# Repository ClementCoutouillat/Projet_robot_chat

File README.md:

# Projet_robot_chat

Projet fait par Quentin Henriet, Bastien Chinianga, Jiang Kaixuan, Jangbo Wang et Clément Coutouillat
Dans ce projet, nous devons réaliser un robot à propulsion différentielle à deux roues pour jouer au jeu du chat et de la souris. Lorsque le robot est le chat, il poursuit la souris, et lorsqu'il est la souris, il fuit le chat. Pour accomplir ce jeu, nous devons réaliser les parties suivantes :

- Le robot doit pouvoir changer de rôle entre chat et souris dans le jeu. Lorsque deux robots entrent en collision, leurs rôles changent - capteur de détection de collision.
- Le robot doit pouvoir se déplacer dans un environnement avec des limites, donc nous avons besoin d'un capteur de détection de bord - capteur de détection de bord.
- Le robot doit pouvoir détecter le chat ou la souris sur le terrain, donc nous avons besoin d'un capteur pour détecter les objets sur le terrain - capteur LIDAR.

## Ydlidar

Nous utilisons le LIDAR YDLIDAR X4 pour détecter l'autre robot sur le terrain.
D'après le manuel de données de YDLIDAR, nous savons que YDLIDAR utilise Uart pour la communication. Dans le manuel de développement, nous pouvons obtenir le format des données du LIDAR, comme illustré ci-dessous :
Lorsque nous envoyons la commande A5 60 au LIDAR, il renvoie une trame de données, dont le format est illustré ci-dessous :

Ensuite, en suivant la méthode d'analyse du manuel de développement, nous obtenons les angles et les distances des obstacles de 0 à 360 degrés autour du robot, ce qui nous permet de localiser l'autre robot.

## Stratégie

Dans le jeu, lorsque le robot est le chat, il doit poursuivre la souris, et lorsqu'il est la souris, il doit fuir le chat. Donc, selon le rôle du robot, nous avons besoin de stratégies différentes pour contrôler le mouvement du robot.

### Stratégie Chat

Lorsque le robot est le chat, il doit poursuivre la souris. Nous devons donc faire bouger le robot dans la direction de la souris. Tout d'abord, nous contrôlons la rotation du robot en calculant la différence d'angle entre le robot et la souris. Lorsque la souris se trouve entre 0 et 180 degrés, nous faisons tourner le robot à gauche. Lorsque l'autre robot se trouve entre 180 et 360 degrés, nous faisons tourner le robot

à droite. Une fois que le robot est orienté correctement, nous le faisons avancer jusqu'à ce qu'il entre en collision avec la souris. À ce moment-là, le rôle du robot change : le robot devient la souris et l'autre robot devient le chat. Nous pouvons alors utiliser la stratégie de la souris pour contrôler le mouvement du robot.

### Stratégie Souris

Lorsque le robot est la souris, il doit fuir le chat. Nous devons donc faire éloigner le robot du chat. Lorsqu'un chat se trouve à moins de 50 cm du robot et qu'il est situé entre 0 et 180 degrés, nous faisons tourner le robot à gauche de 90 degrés, puis le faisons avancer sur une certaine distance avant de le faire tourner à droite de 90 degrés. Cela permet au robot de s'éloigner du chat. Lorsque la distance entre le robot et le chat dépasse 50 cm, nous arrêtons le mouvement du robot. Lorsque le chat est situé entre 180 et 360 degrés, nous faisons tourner le robot à droite de 90 degrés, puis à gauche de 90 degrés, pour lui permettre de s'éloigner du chat.

## Moteur

Nous utilisons un robot à propulsion différentielle à deux roues, donc nous devons contrôler la vitesse des roues gauche et droite pour diriger le robot. Nous utilisons un moteur à courant continu à engrenages avec encodeur, dont la vitesse maximale est de 300 RPM.

### Avancer

Pour faire avancer le robot en ligne droite, nous contrôlons les vitesses des roues gauche et droite pour qu'elles soient identiques.

### Tourner

Le robot tourne en contrôlant la différence de vitesse entre les roues gauche et droite. Lorsque les vitesses des roues sont différentes, le robot tourne.

Nous utilisons une vitesse fixe pour contrôler la direction du robot. Lorsque le robot doit tourner à gauche, nous fixons la vitesse de la roue gauche à 0 et celle de la roue droite à la vitesse maximale. Lorsque le robot doit tourner à droite, nous fixons la vitesse de la roue droite à 0 et celle de la roue gauche à la vitesse maximale. Le temps nécessaire pour tourner est calculé avec la formule suivante :

<br />
leftWheelLinearVelocity = wheelDiameter * PI * leftWheelRPM / 60 ;
<br />
rightWheelLinearVelocity = wheelDiameter * PI * rightWheelRPM / 60 ;
<br />
angulaVelocity = (leftWheellinearVelocity - rightWheellinearVelocity) / WheelDistance ;
<br />
Timer = Angle(0-360) *PI / 180 / angulaVelocity ;

### Distance Control

La distance parcourue par le robot est contrôlée en gérant le temps de fonctionnement du robot. Lorsque le robot fonctionne pendant le temps que nous avons défini, il s'arrête. Cela permet de contrôler la distance parcourue par le robot. Le temps est calculé avec la formule suivante :
<br />
Timer = Distance / (WheelDiameter \* PI) / Vitesse ;

### Commande

Dans notre code pour manipuler le moteur, nous avons écrit deux fonctions. La première permet de contrôler directement la vitesse du moteur. Pour que le robot réponde plus rapidement aux commandes d'arrêt et d'accélération, nous avons également écrit une seconde fonction d'asservissement, qui utilise l'algorithme PID pour contrôler la rotation du moteur. Toutes les 100 ms, nous calculons la vitesse actuelle et fournissons un feedback sur la vitesse pour nous informer de la vitesse actuelle de rotation du moteur, ce qui nous permet de calculer plus précisément la position actuelle du robot et la distance parcourue. L'entrée du contrôleur PID est la vitesse cible du robot, et la sortie est la vitesse des roues gauche et droite du robot.

## Border

Pour les capteurs de bordure nous avons décidé d'utiliser les interruptions extérieures afin que la plus grande priorité possible et ne pas être interrompu durant le traitement de la détection de bordure. L'objectif était de pouvoir reculer et de tourner de 90 ou 180 degrés. Des tests ont été effectué sur une autre carte afin de vérifier le bon fonctionnement des fonctions. Malheureusement, les fonctions n'ont pas été implémenté sur la carte car les capteurs infrarouges étaient inutilisables et nous n'avions pas d'autres.

## Contact

Les capteurs de contact sont aussi branché sur les entrées GPIO du microprocesseur. Le contact permettant de gérer le mode chat ou souris, nous avons aussi décidé de les mettre en interruptions extérieur car ça simplifie le code avec juste une interruption qui préempte le code et une gestion de l'interruption. Il faut aussi mettre l'interruption des capteurs de bordure avec une plus haute priorité car c'est plus important de garder le robot sur le terrain que de savoir si on se fait toucher. Dans l'IOC il faut faire attention à comment sont régler les GPIO. Ils sont soit en pull-up ou pull-down. Afin de pour pouvoir résoudre le problème du fonctionnement des  capteurs de contact nous avons décidé de "simuler" le fait d'être touchés par un autre robot. C'est-à-dire quand nous sommes trop proches d'un autre robot nous considérons que nous avons été touché par celui-ci, car sinon le robot ne change jamais d'état.

## Accéléromètre

Au cours du projet nous avons utilisé deux cartes différentes. Sur la première, nous avions pensé à utiliser une centrale inertielle donc un accéléromètre et un gyroscope. Nous avons donc commencé l'écriture d'un driver( un .c et un .h) pour utiliser cet IMU. Malheureusement sur la nouvelle carte il n'y avait plus la possibilité d'utiliser un IMU, et vu l'inutilité de cette partie nous avons décidé de ne pas la mettre sur le github mais de quand même  mentionner le fait qu'un début de driver a été fait.

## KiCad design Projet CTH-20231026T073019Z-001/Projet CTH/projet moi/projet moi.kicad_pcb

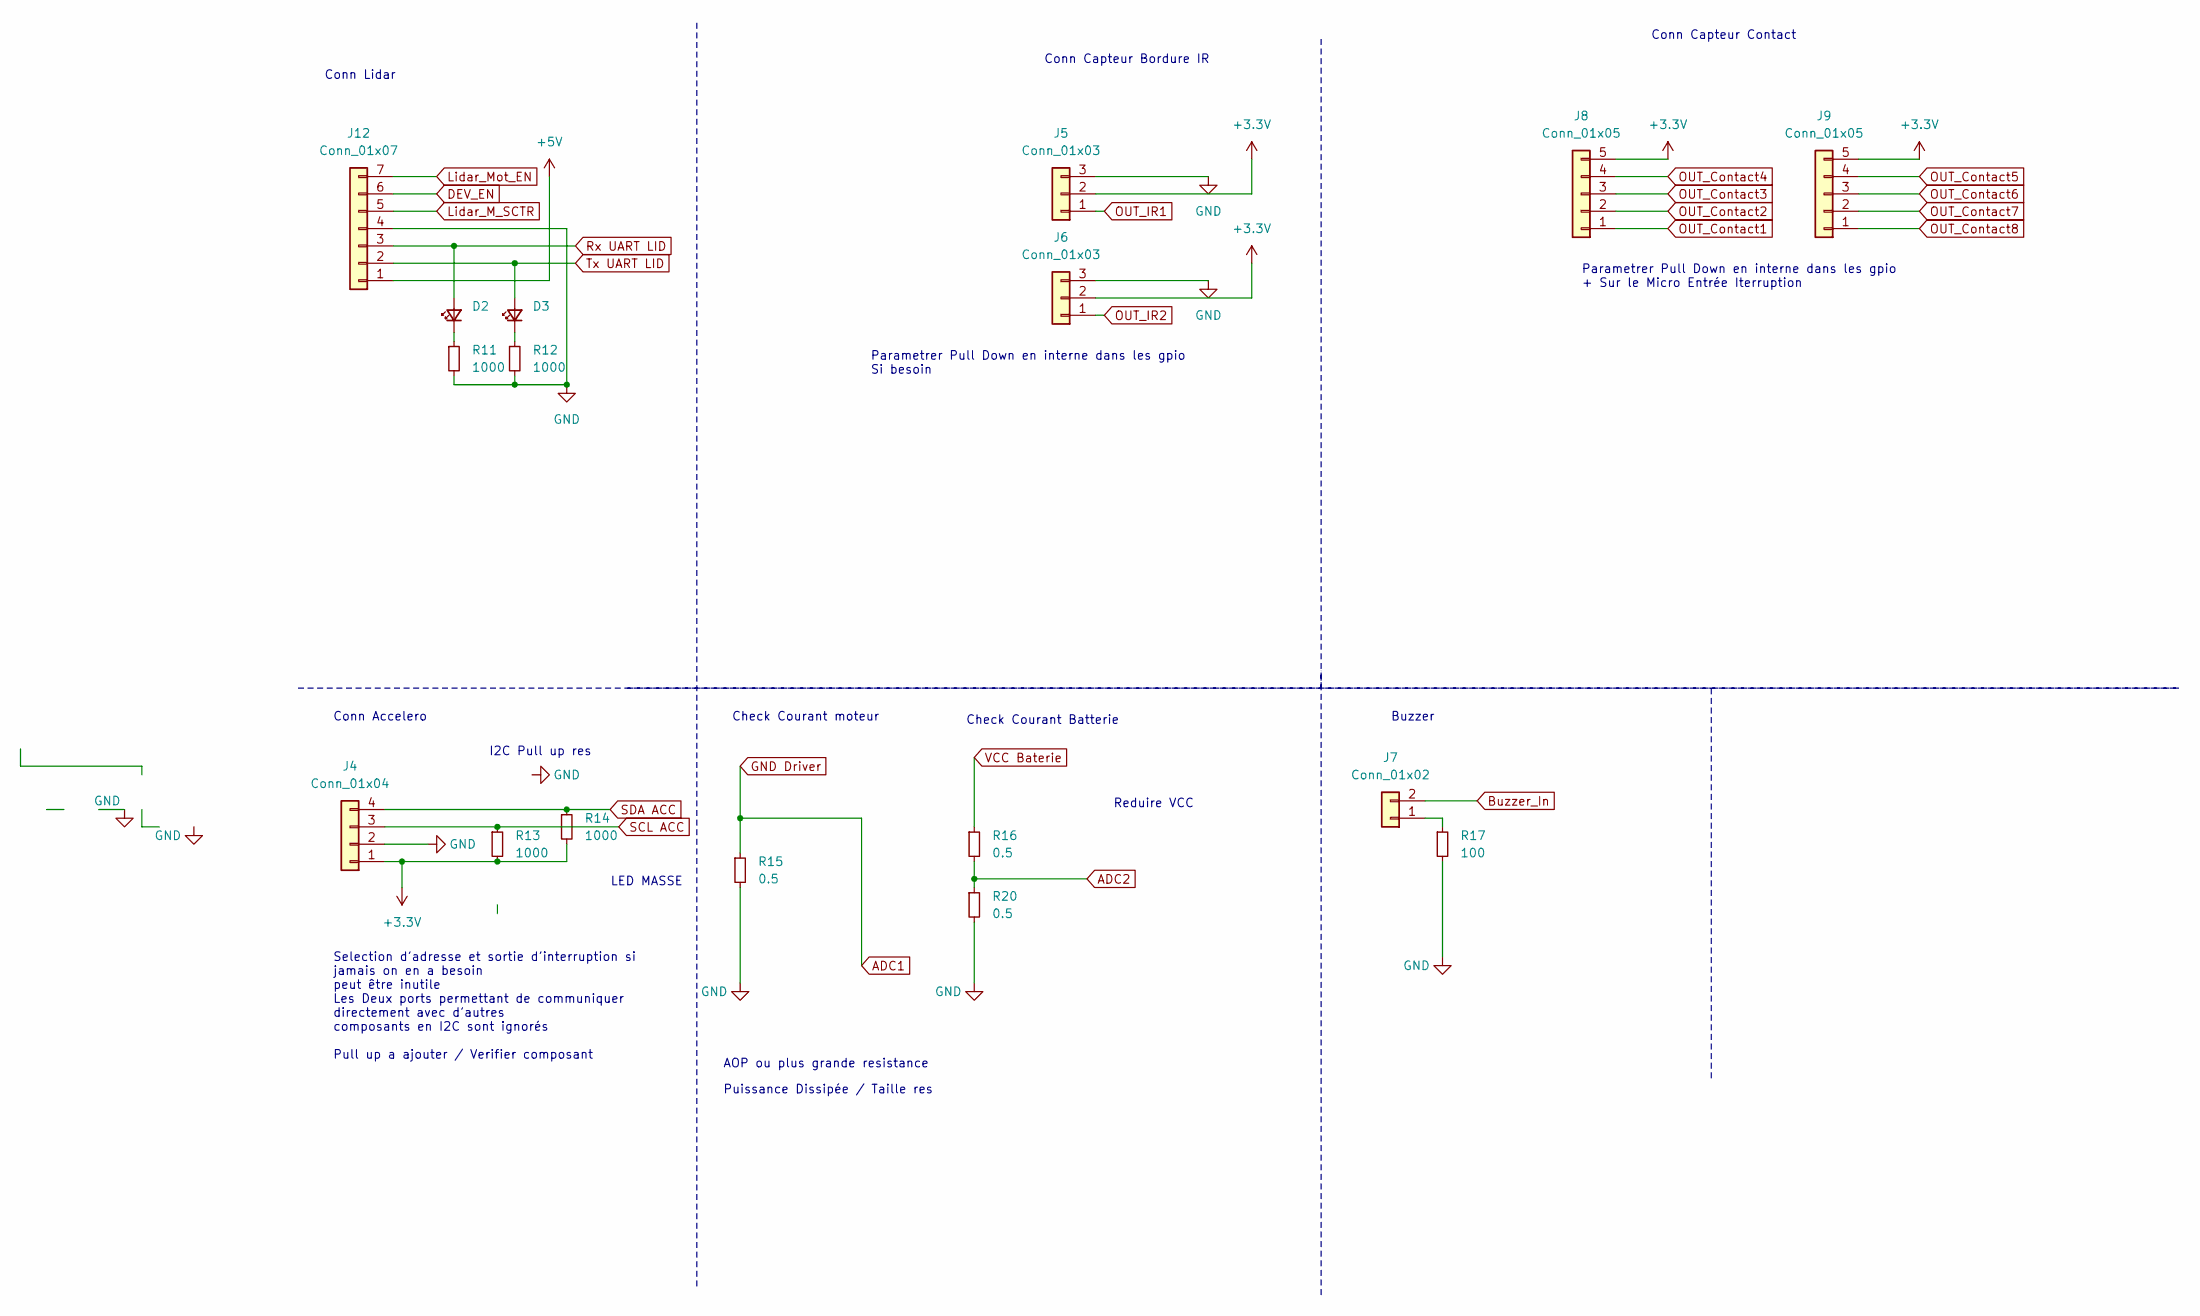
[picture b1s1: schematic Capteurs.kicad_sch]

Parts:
D2, D3: LED_Small; LED_0603_1608Metric_Pad1.05x0.95mm_HandSolder
J4: Conn_01x04; JST_EH_S4B-EH_1x04_P2.50mm_Horizontal
J5, J6: Conn_01x03; JST_XH_S3B-XH-A_1x03_P2.50mm_Horizontal
J7: Conn_01x02; JST_XH_S2B-XH-A_1x02_P2.50mm_Horizontal
J8, J9: Conn_01x05; JST_XH_S5B-XH-A_1x05_P2.50mm_Horizontal
J12: Conn_01x07; JST_XH_S7B-XH-A_1x07_P2.50mm_Horizontal
R11, R12, R13, R14: 1000; R_0603_1608Metric_Pad0.98x0.95mm_HandSolder
R15, R16, R20: 0.5; R_0603_1608Metric_Pad0.98x0.95mm_HandSolder
R17: 100; R_0603_1608Metric_Pad0.98x0.95mm_HandSolder

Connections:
7.2V: R16.1; also elsewhere on the board
+3.3V: J4.1, J5.2, J6.2, J8.5, J9.5, R13.2, R14.2; also elsewhere on the board
+5V: J12.1; also elsewhere on the board
ADC1: R15.1; also elsewhere on the board
ADC2: R16.2, R20.1; also elsewhere on the board
DEV_EN: J12.6; also elsewhere on the board
GND: J4.2, J5.3, J6.3, J12.4, R11.2, R12.2, R15.2, R17.2, R20.2; also elsewhere on the board
Lidar_M_SCTR: J12.5
Lidar_Mot_EN: J12.7
unnamed: D2.1 (K), R11.1
unnamed: D3.1 (K), R12.1
unnamed: J7.1, R17.1
OUT_Contact1: J8.1; also elsewhere on the board
OUT_Contact2: J8.2; also elsewhere on the board
OUT_Contact3: J8.3; also elsewhere on the board
OUT_Contact4: J8.4; also elsewhere on the board
OUT_Contact5: J9.4; also elsewhere on the board
OUT_Contact6: J9.3; also elsewhere on the board
OUT_Contact7: J9.2; also elsewhere on the board
OUT_Contact8: J9.1; also elsewhere on the board
OUT_IR1: J5.1; also elsewhere on the board
OUT_IR2: J6.1; also elsewhere on the board
Rx UART LID: D2.2 (A), J12.3; also elsewhere on the board
SCL ACC: J4.3, R13.1; also elsewhere on the board
SDA ACC: J4.4, R14.1; also elsewhere on the board
Tx UART LID: D3.2 (A), J12.2; also elsewhere on the board

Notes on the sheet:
Reduire VCC
Check Courant moteur
Buzzer
Parametrer Pull Down en interne dans les gpio + Sur le Micro Entrée Iterruption
Check Courant Batterie
AOP ou plus grande resistance
Puissance Dissipée / Taille res
Conn Lidar
Conn Accelero
Conn Capteur Contact
Parametrer Pull Down en interne dans les gpio Si besoin
I2C Pull up res
Selection d'adresse et sortie d'interruption si jamais on en a besoin peut être inutile Les Deux ports permettant de communiquer directement avec d'autres composants en I2C sont ignorés Pull up a ajouter / Verifier composant
LED MASSE
Conn Capteur Bordure IR

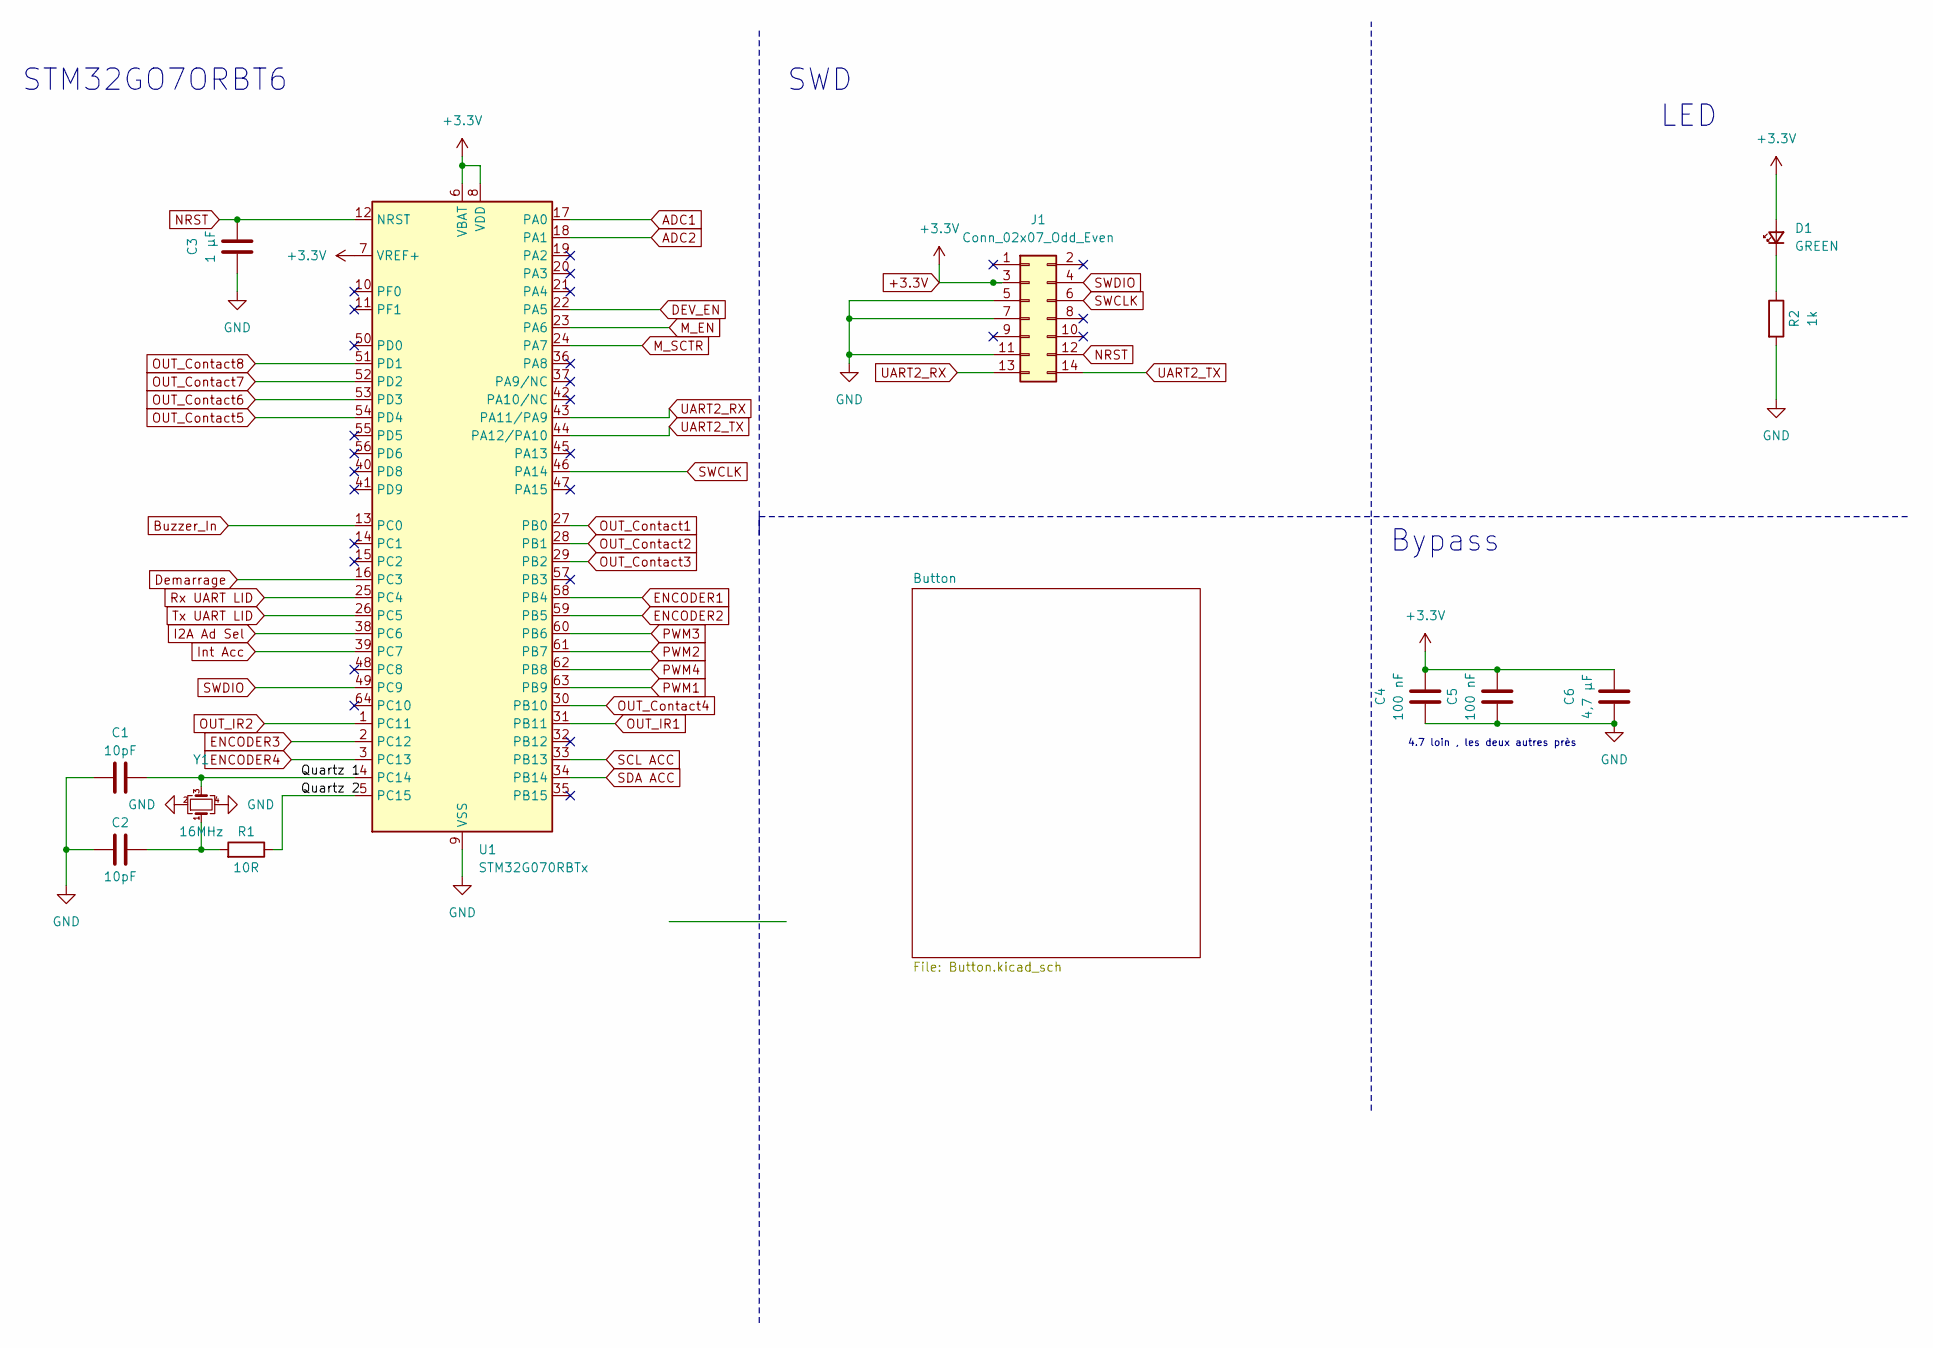
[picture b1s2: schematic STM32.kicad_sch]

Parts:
C1, C2: 10pF; C_0603_1608Metric_Pad1.08x0.95mm_HandSolder
C3: 1 µF; C_0603_1608Metric_Pad1.08x0.95mm_HandSolder
C4, C5: 100 nF; C_0603_1608Metric_Pad1.08x0.95mm_HandSolder
C6: 4,7 µF; C_0603_1608Metric_Pad1.08x0.95mm_HandSolder
D1: GREEN; LED_0603_1608Metric_Pad1.05x0.95mm_HandSolder
J1: Conn_02x07_Odd_Even; Molex_Nano-Fit_105314-xx14_2x07_P2.50mm_Horizontal
R1: 10R; R_0603_1608Metric_Pad0.98x0.95mm_HandSolder
R2: 1k; R_0603_1608Metric_Pad0.98x0.95mm_HandSolder
U1: STM32G070RBTx; LQFP-64_10x10mm_P0.5mm
Y1: 16MHz; Crystal_SMD_EuroQuartz_MT-4Pin_3.2x2.5mm

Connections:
+3.3V: C4.2, C5.2, C6.2, D1.2 (A), J1.3, U1.6 (VBAT), U1.7 (VREF+), U1.8 (VDD); also elsewhere on the board
/STM32/Quartz 1: C1.2, U1.4 (PC14), Y1.3
/STM32/Quartz 2: R1.1, U1.5 (PC15)
ADC1: U1.17 (PA0); also elsewhere on the board
ADC2: U1.18 (PA1); also elsewhere on the board
Buzzer_In: U1.13 (PC0)
DEV_EN: U1.22 (PA5); also elsewhere on the board
Demarrage: U1.16 (PC3); also elsewhere on the board
ENCODER1: U1.58 (PB4); also elsewhere on the board
ENCODER2: U1.59 (PB5); also elsewhere on the board
ENCODER3: U1.2 (PC12); also elsewhere on the board
ENCODER4: U1.3 (PC13); also elsewhere on the board
GND: C1.1, C2.1, C3.1, C4.1, C5.1, C6.1, J1.5, J1.7, J1.11, R2.2, U1.9 (VSS), Y1.2, Y1.4; also elsewhere on the board
I2A Ad Sel: U1.38 (PC6)
Int Acc: U1.39 (PC7)
M_EN: U1.23 (PA6)
M_SCTR: U1.24 (PA7)
NRST: C3.2, J1.12, U1.12 (NRST); also elsewhere on the board
unnamed: C2.2, R1.2, Y1.1
unnamed: D1.1 (K), R2.1
OUT_Contact1: U1.27 (PB0); also elsewhere on the board
OUT_Contact2: U1.28 (PB1); also elsewhere on the board
OUT_Contact3: U1.29 (PB2); also elsewhere on the board
OUT_Contact4: U1.30 (PB10); also elsewhere on the board
OUT_Contact5: U1.54 (PD4); also elsewhere on the board
OUT_Contact6: U1.53 (PD3); also elsewhere on the board
OUT_Contact7: U1.52 (PD2); also elsewhere on the board
OUT_Contact8: U1.51 (PD1); also elsewhere on the board
OUT_IR1: U1.31 (PB11); also elsewhere on the board
OUT_IR2: U1.1 (PC11); also elsewhere on the board
PWM1: U1.63 (PB9); also elsewhere on the board
PWM2: U1.61 (PB7); also elsewhere on the board
PWM3: U1.60 (PB6); also elsewhere on the board
PWM4: U1.62 (PB8); also elsewhere on the board
Rx UART LID: U1.25 (PC4); also elsewhere on the board
SCL ACC: U1.33 (PB13); also elsewhere on the board
SDA ACC: U1.34 (PB14); also elsewhere on the board
SWCLK: J1.6, U1.46 (PA14)
SWDIO: J1.4, U1.49 (PC9)
Tx UART LID: U1.26 (PC5); also elsewhere on the board
UART2_RX: J1.13, U1.43 (PA11/PA9)
UART2_TX: J1.14, U1.44 (PA12/PA10)

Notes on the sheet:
STM32GO7ORBT6
Bypass
LED
SWD
4.7 loin , les deux autres près

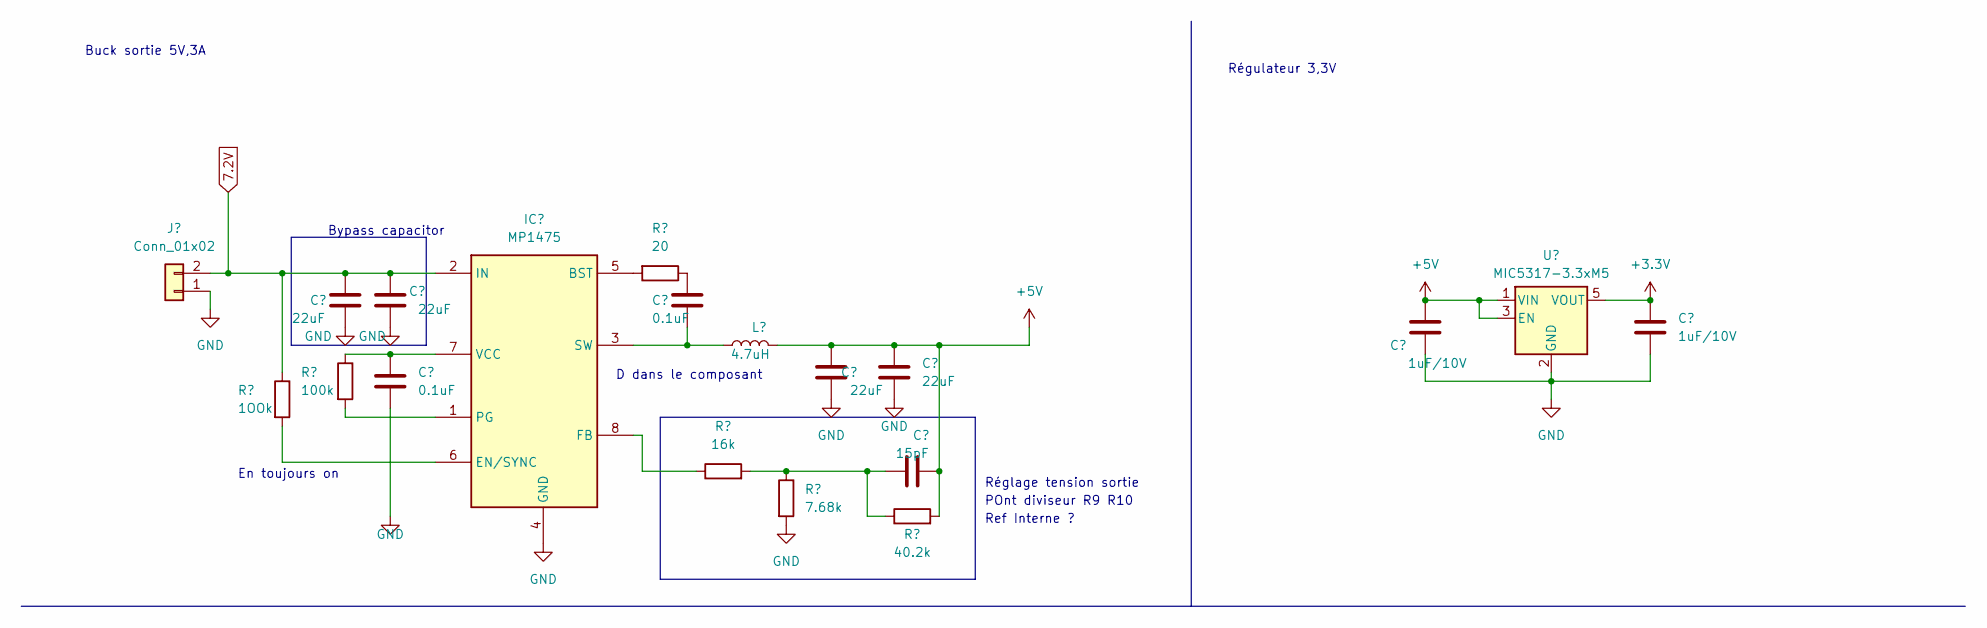
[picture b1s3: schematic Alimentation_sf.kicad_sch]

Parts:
C11, C12, C15, C16: 22uF; C_0603_1608Metric_Pad1.08x0.95mm_HandSolder
C13, C14: 0.1uF; C_0603_1608Metric_Pad1.08x0.95mm_HandSolder
C17: 15pF; C_0603_1608Metric_Pad1.08x0.95mm_HandSolder
C18, C19: 1uF/10V; C_0603_1608Metric_Pad1.08x0.95mm_HandSolder
IC1: MP1475; SOT65P280X100-8N; Mouser Part Number 946-MP1475SGJ-P
J2: Conn_01x02; JST_XH_S2B-XH-A_1x02_P2.50mm_Horizontal
L2: 4.7uH; L_0603_1608Metric_Pad1.05x0.95mm_HandSolder
R5: 1OOk; R_0603_1608Metric_Pad0.98x0.95mm_HandSolder
R6: 100k; R_0603_1608Metric_Pad0.98x0.95mm_HandSolder
R7: 20; R_0603_1608Metric_Pad0.98x0.95mm_HandSolder
R8: 16k; R_0603_1608Metric_Pad0.98x0.95mm_HandSolder
R9: 7.68k; R_0603_1608Metric_Pad0.98x0.95mm_HandSolder
R10: 40.2k; R_0603_1608Metric_Pad0.98x0.95mm_HandSolder
U2: MIC5317-3.3xM5; SOT-23-5

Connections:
7.2V: C11.1, C12.1, IC1.2 (IN), J2.2, R5.1; also elsewhere on the board
+3.3V: C19.1, U2.5 (VOUT); also elsewhere on the board
+5V: C15.1, C16.1, C17.2, C18.1, L2.2, R10.2, U2.1 (VIN), U2.3 (EN); also elsewhere on the board
GND: C11.2, C12.2, C13.2, C15.2, C16.2, C18.2, C19.2, IC1.4 (GND), J2.1, R9.2, U2.2 (GND); also elsewhere on the board
unnamed: C14.1, R7.1
unnamed: C17.1, R8.2, R9.1, R10.1
unnamed: IC1.5 (BST), R7.2
unnamed: IC1.6 (EN/SYNC), R5.2
unnamed: IC1.8 (FB), R8.1
unnamed: IC1.1 (PG), R6.2
unnamed: C14.2, IC1.3 (SW), L2.1
unnamed: C13.1, IC1.7 (VCC), R6.1

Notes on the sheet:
Bypass capacitor
POnt diviseur R9 R10
D dans le composant
En toujours on
Réglage tension sortie
Buck sortie 5V,3A
Régulateur 3,3V
Ref Interne ?

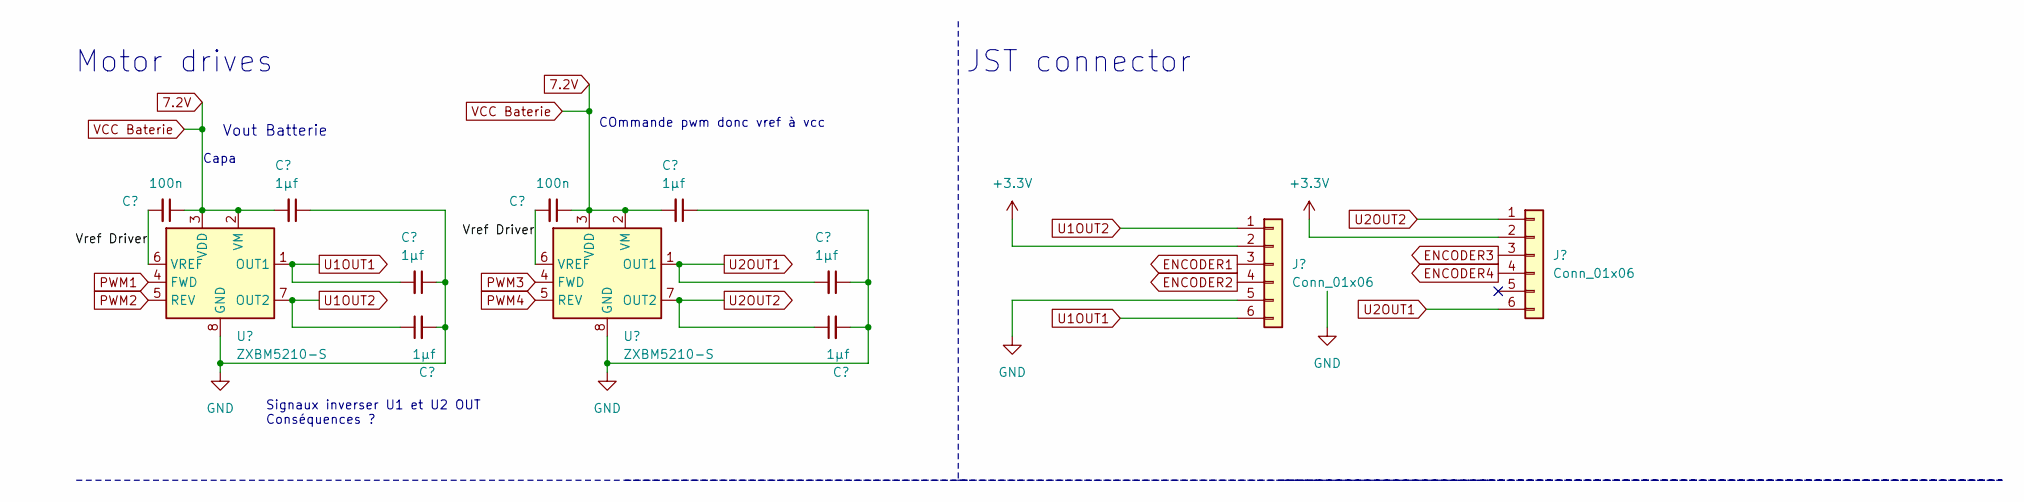
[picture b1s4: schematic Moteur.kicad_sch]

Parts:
C20, C21, C22, C23, C24, C25: 1µf; C_0603_1608Metric_Pad1.08x0.95mm_HandSolder
C27, C28: 100n; C_0603_1608Metric_Pad1.08x0.95mm_HandSolder
J10, J11: Conn_01x06; JST_XH_S6B-XH-A_1x06_P2.50mm_Horizontal
U3, U4: ZXBM5210-S; SOIC-8_3.9x4.9mm_P1.27mm

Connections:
7.2V: C20.2, C23.2, C27.1, C28.1, U3.2 (VM), U3.3 (VDD), U4.2 (VM), U4.3 (VDD); also elsewhere on the board
+3.3V: J10.2, J11.2; also elsewhere on the board
/Moteur/Vref Driver: C27.2, C28.2, U3.6 (VREF), U4.6 (VREF)
ENCODER1: J10.3; also elsewhere on the board
ENCODER2: J10.4; also elsewhere on the board
ENCODER3: J11.3; also elsewhere on the board
ENCODER4: J11.4; also elsewhere on the board
GND: C20.1, C21.1, C22.2, C23.1, C24.1, C25.2, J10.5, U3.8 (GND), U4.8 (GND); also elsewhere on the board
PWM1: U3.4 (FWD); also elsewhere on the board
PWM2: U3.5 (REV); also elsewhere on the board
PWM3: U4.4 (FWD); also elsewhere on the board
PWM4: U4.5 (REV); also elsewhere on the board
U1OUT1: C21.2, J10.6, U3.1 (OUT1)
U1OUT2: C22.1, J10.1, U3.7 (OUT2)
U2OUT1: C24.2, J11.6, U4.1 (OUT1)
U2OUT2: C25.1, J11.1, U4.7 (OUT2)

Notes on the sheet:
JST connector
Capa
Vout Batterie
Signaux inverser U1 et U2 OUT Conséquences ?
COmmande pwm donc vref à vcc
Motor drives

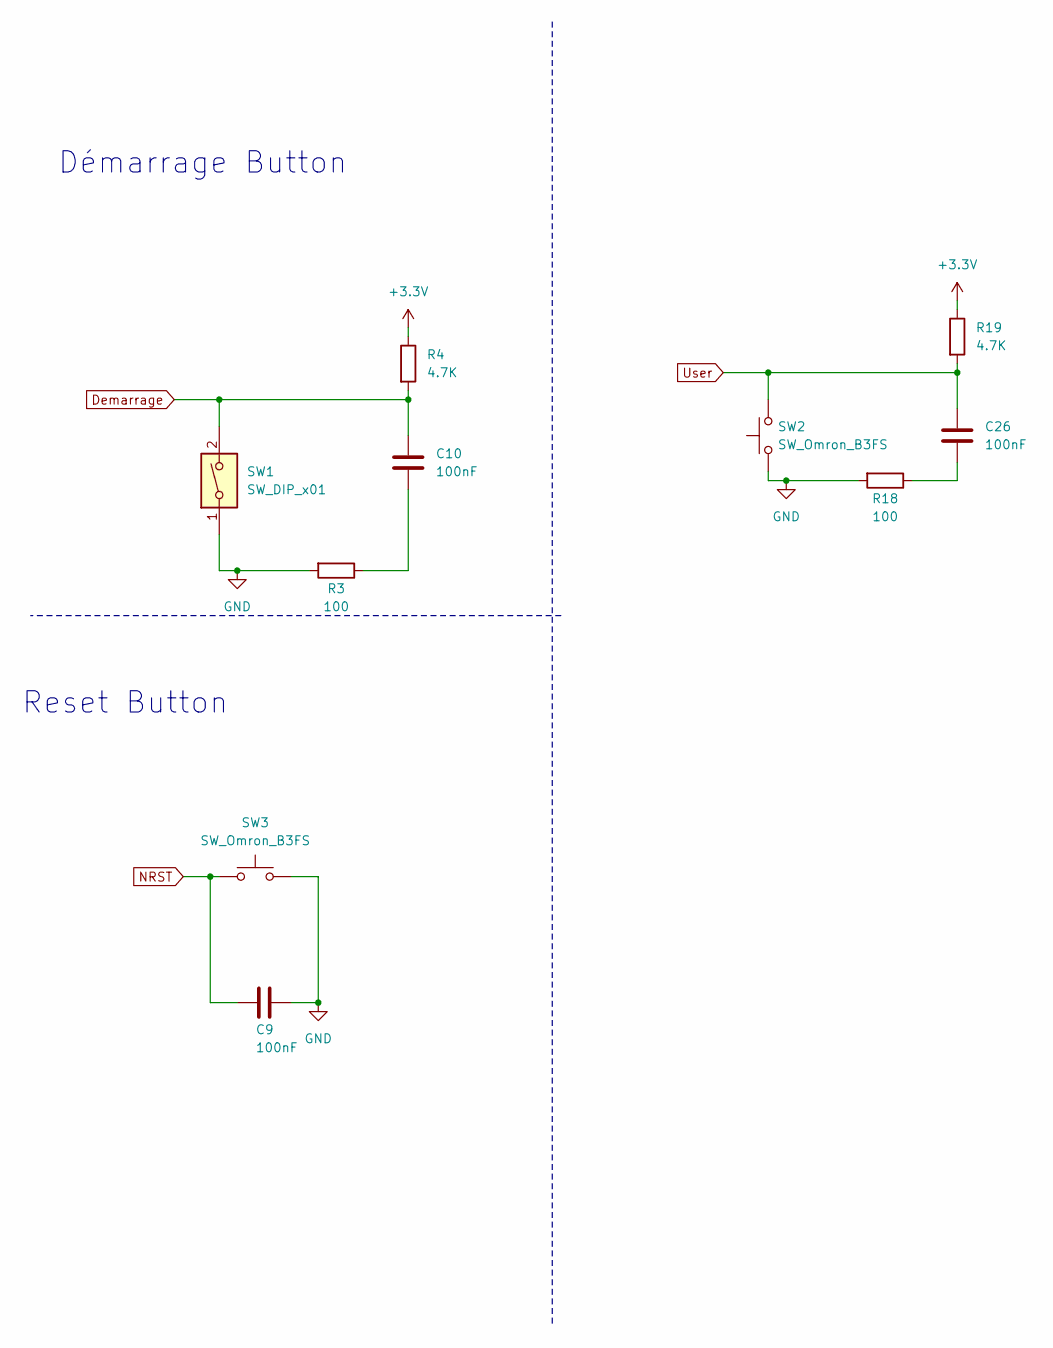
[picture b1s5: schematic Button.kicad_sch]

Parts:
C9, C10, C26: 100nF; C_0603_1608Metric_Pad1.08x0.95mm_HandSolder
R3, R18: 100; R_0603_1608Metric_Pad0.98x0.95mm_HandSolder
R4, R19: 4.7K; R_0603_1608Metric_Pad0.98x0.95mm_HandSolder
SW1: SW_DIP_x01; SW_SPST_B3U-1000P
SW2, SW3: SW_Omron_B3FS; SW_SPST_B3U-1000P

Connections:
+3.3V: R4.1, R19.1; also elsewhere on the board
Demarrage: C10.1, R4.2, SW1.2; also elsewhere on the board
GND: C9.1, R3.2, R18.2, SW1.1, SW2.1, SW3.2; also elsewhere on the board
NRST: C9.2, SW3.1; also elsewhere on the board
unnamed: C10.2, R3.1
unnamed: C26.2, R18.1
User: C26.1, R19.2, SW2.2

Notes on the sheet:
Démarrage Button
Reset Button

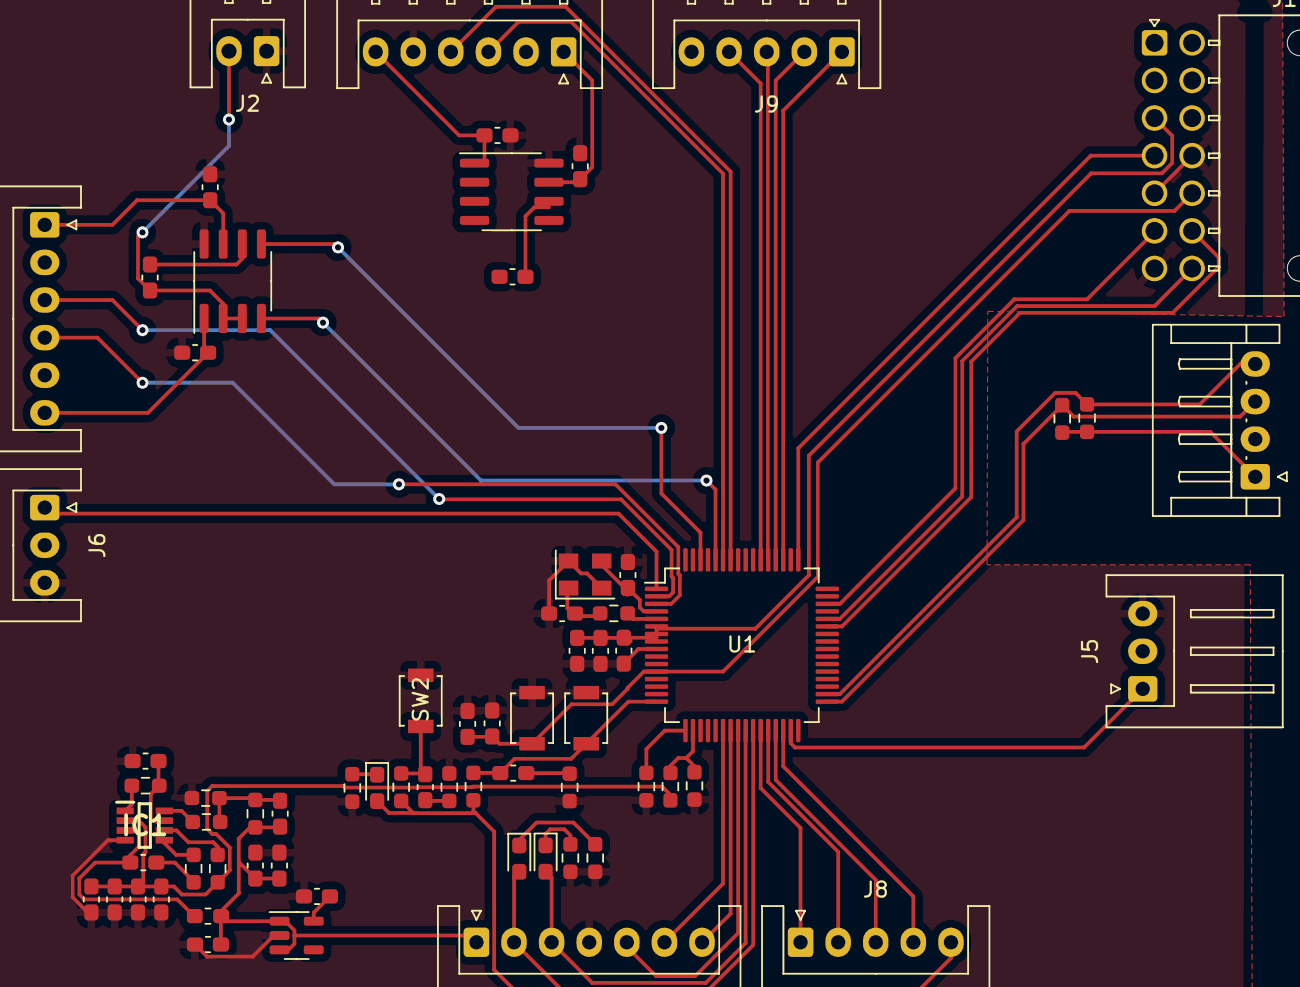
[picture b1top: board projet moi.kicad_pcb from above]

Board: 4 copper layers, 68 parts (0 on the bottom side), 57 nets.

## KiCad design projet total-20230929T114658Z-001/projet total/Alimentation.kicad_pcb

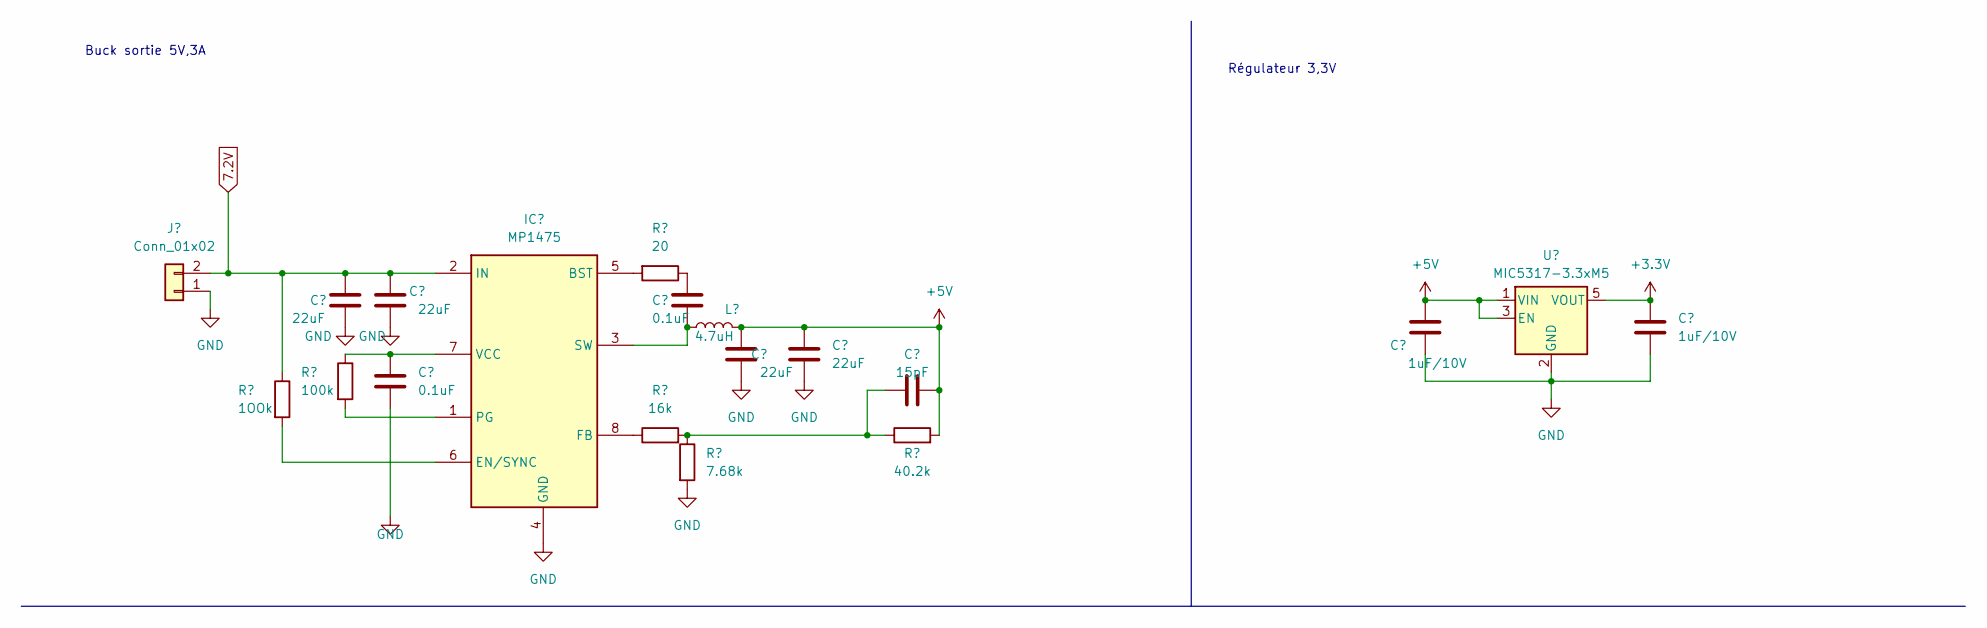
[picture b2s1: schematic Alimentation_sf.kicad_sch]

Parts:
C11, C12, C15, C16: 22uF; C_0603_1608Metric_Pad1.08x0.95mm_HandSolder
C13, C14: 0.1uF; C_0603_1608Metric_Pad1.08x0.95mm_HandSolder
C17: 15pF; C_0603_1608Metric_Pad1.08x0.95mm_HandSolder
C18, C19: 1uF/10V; C_0603_1608Metric_Pad1.08x0.95mm_HandSolder
IC1: MP1475; SOT65P280X100-8N; Mouser Part Number 946-MP1475SGJ-P
J2: Conn_01x02; PinSocket_1x02_P2.54mm_Vertical
L2: 4.7uH; L_0603_1608Metric_Pad1.05x0.95mm_HandSolder
R5: 1OOk; R_0603_1608Metric_Pad0.98x0.95mm_HandSolder
R6: 100k; R_0603_1608Metric_Pad0.98x0.95mm_HandSolder
R7: 20; R_0603_1608Metric_Pad0.98x0.95mm_HandSolder
R8: 16k; R_0603_1608Metric_Pad0.98x0.95mm_HandSolder
R9: 7.68k; R_0603_1608Metric_Pad0.98x0.95mm_HandSolder
R10: 40.2k; R_0603_1608Metric_Pad0.98x0.95mm_HandSolder
U2: MIC5317-3.3xM5; SOT-23-5

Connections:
7.2V: C11.1, C12.1, IC1.2 (IN), J2.2, R5.1; also elsewhere on the board
+5V: C15.1, C16.1, C17.2, C18.1, L2.2, R10.2, U2.1 (VIN), U2.3 (EN); also elsewhere on the board
GND: C11.2, C12.2, C13.2, C15.2, C16.2, C18.2, C19.2, IC1.4 (GND), J2.1, R9.2, U2.2 (GND); also elsewhere on the board
unnamed: C14.1, R7.1
unnamed: C17.1, R8.2, R9.1, R10.1
unnamed: IC1.5 (BST), R7.2
unnamed: IC1.6 (EN/SYNC), R5.2
unnamed: IC1.8 (FB), R8.1
unnamed: IC1.1 (PG), R6.2
unnamed: C14.2, IC1.3 (SW), L2.1
unnamed: C13.1, IC1.7 (VCC), R6.1

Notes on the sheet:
Buck sortie 5V,3A
Régulateur 3,3V

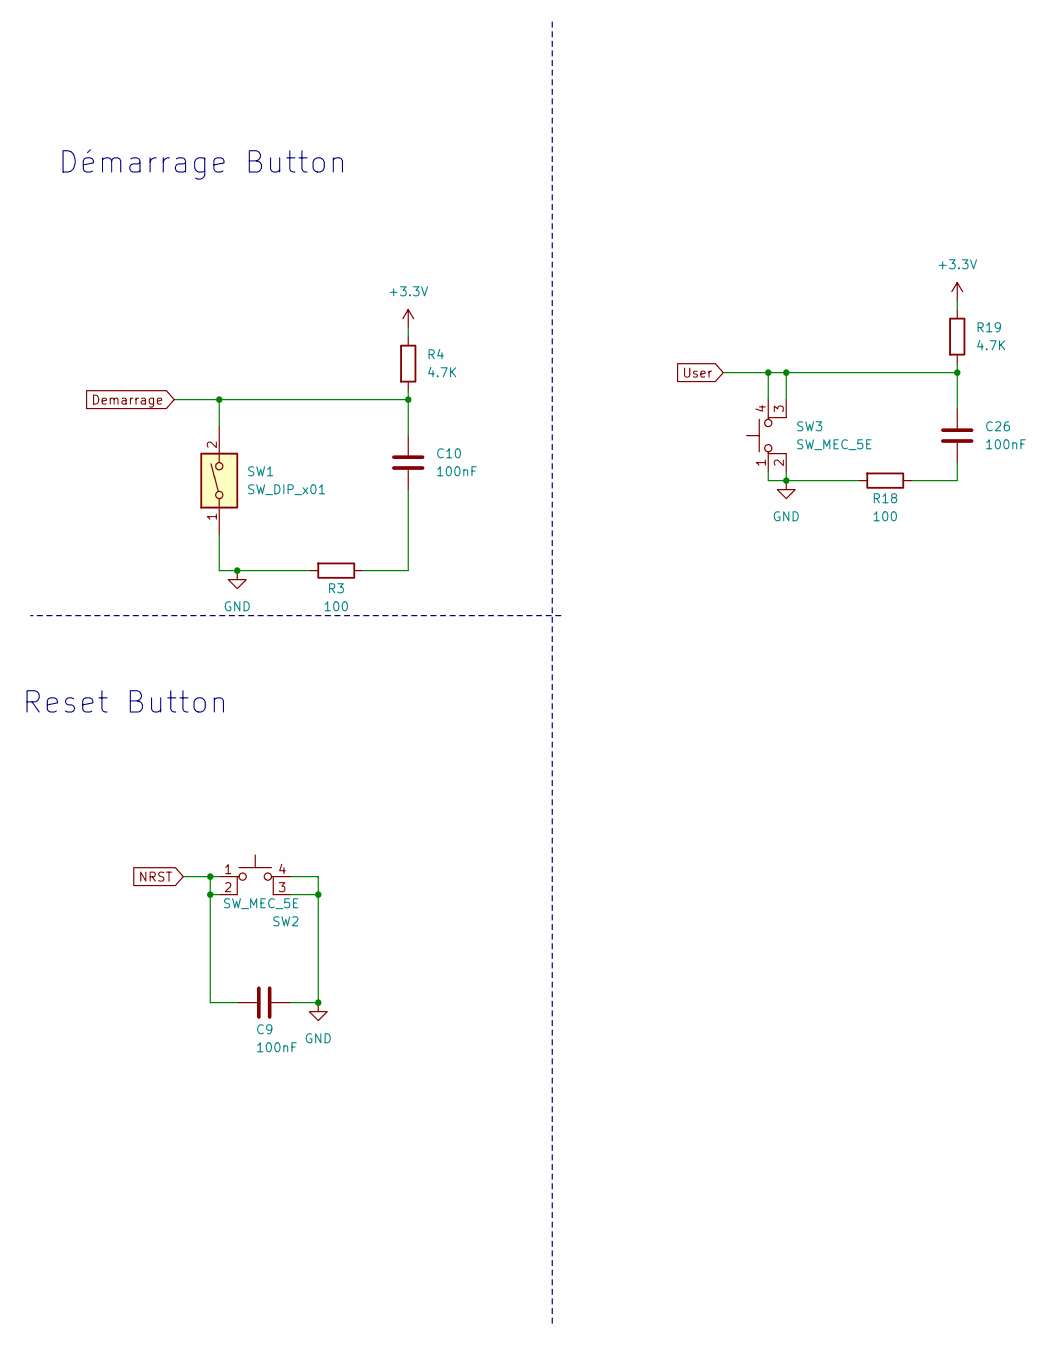
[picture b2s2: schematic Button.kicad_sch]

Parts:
C9, C10, C26: 100nF; C_0603_1608Metric_Pad1.08x0.95mm_HandSolder
R3, R18: 100; R_0603_1608Metric_Pad0.98x0.95mm_HandSolder
R4, R19: 4.7K; R_0603_1608Metric_Pad0.98x0.95mm_HandSolder
SW1: SW_DIP_x01; SW_SPST_B3U-1000P
SW2, SW3: SW_MEC_5E; SW_SPST_B3U-1000P

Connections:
Demarrage: C10.1, R4.2, SW1.2; also elsewhere on the board
GND: C9.1, R3.2, R18.2, SW1.1, SW2.3 (K), SW2.4 (A), SW3.1, SW3.2; also elsewhere on the board
NRST: C9.2, SW2.1, SW2.2; also elsewhere on the board
unnamed: C10.2, R3.1
unnamed: C26.2, R18.1
User: C26.1, R19.2, SW3.3 (K), SW3.4 (A)

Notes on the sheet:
Démarrage Button
Reset Button
